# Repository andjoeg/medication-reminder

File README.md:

# medication-reminder
A device that reminds you to take medications based on a configurable daily schedule.

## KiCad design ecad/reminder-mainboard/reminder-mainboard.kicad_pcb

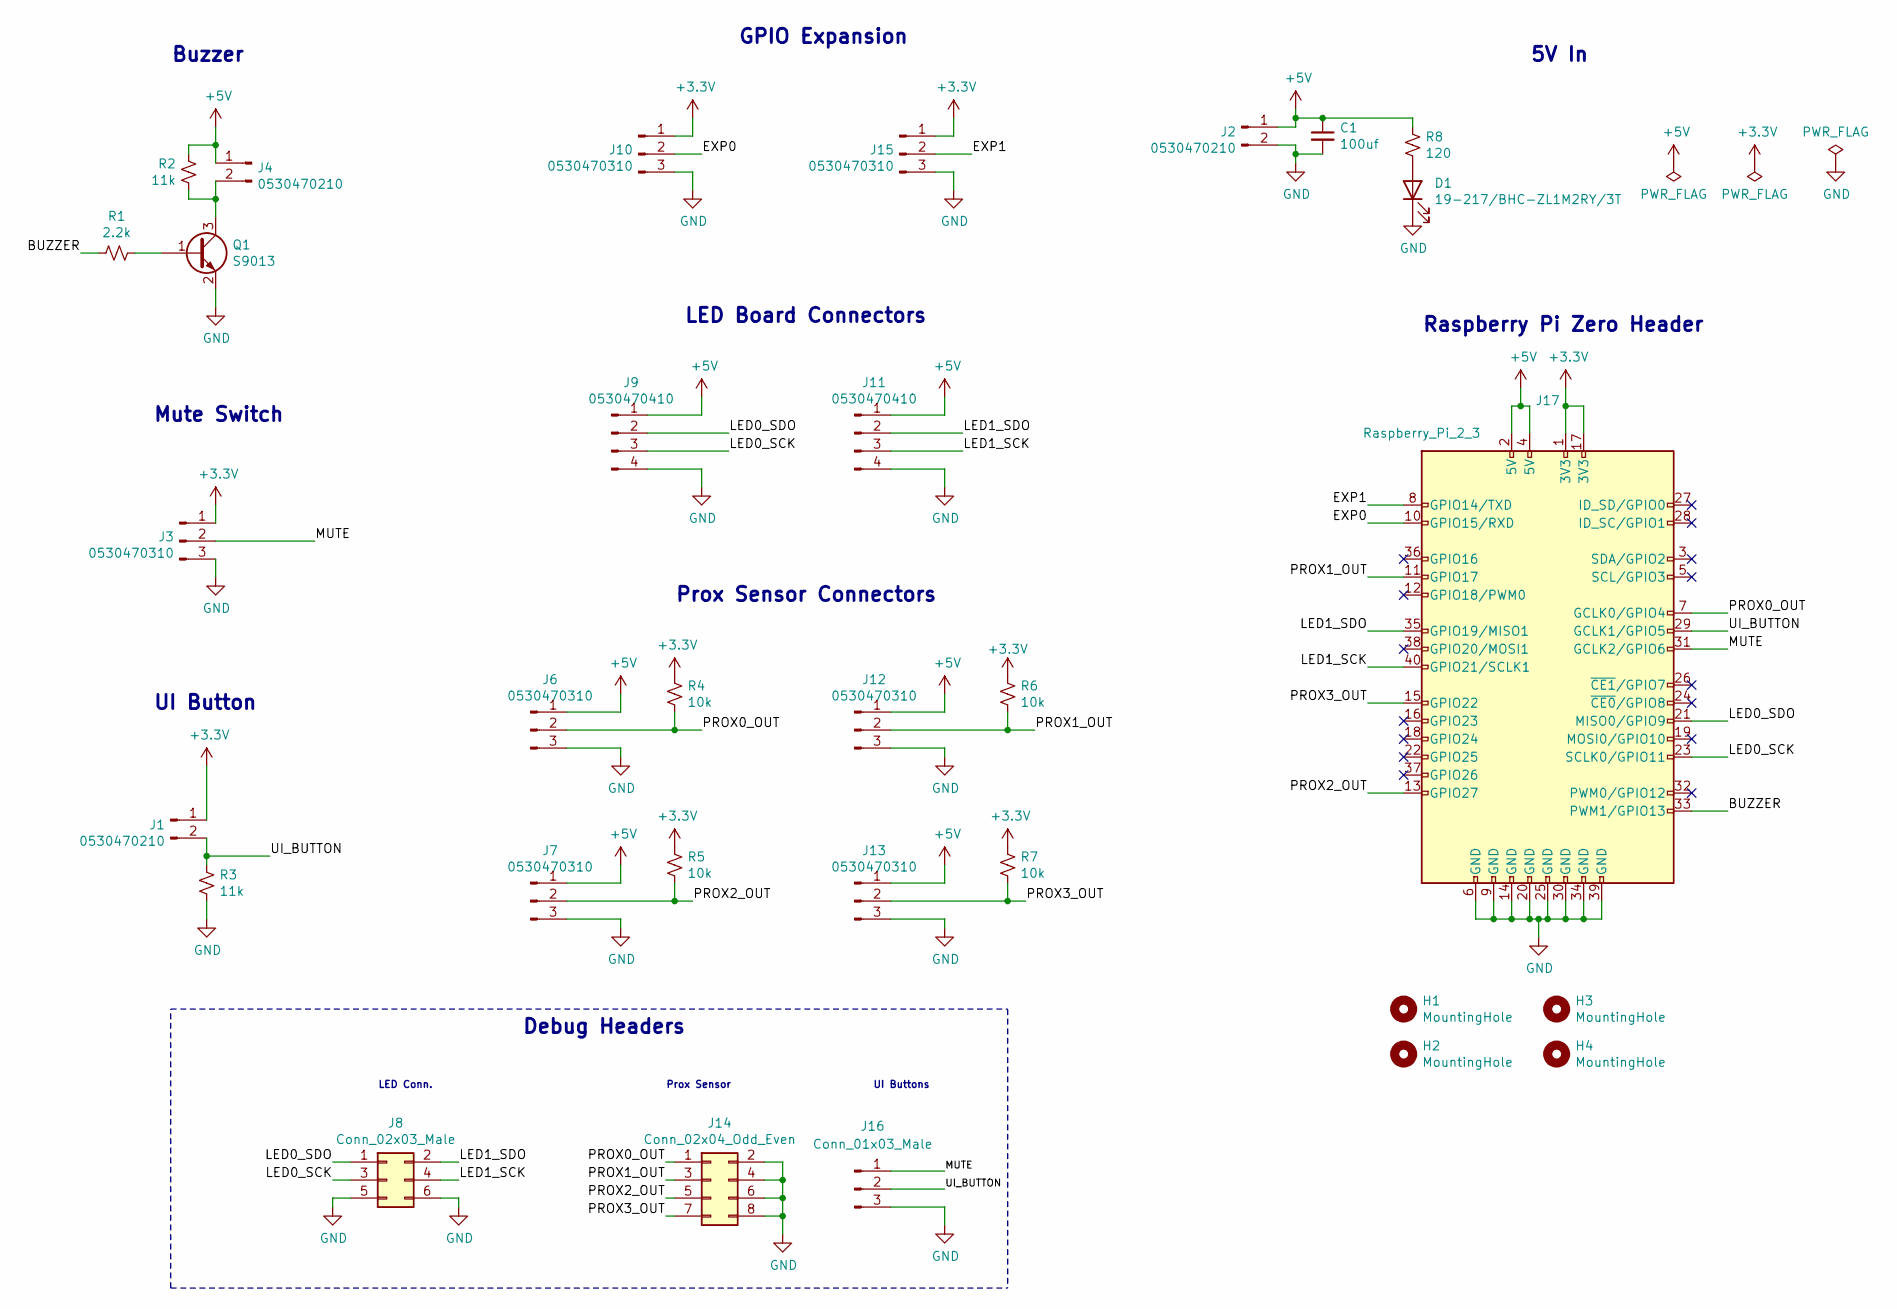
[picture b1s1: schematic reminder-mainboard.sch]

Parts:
C1: 100uf; CP_EIA-3528-21_Kemet-B; LCSC Part Number C16133
D1: 19-217/BHC-ZL1M2RY/3T; LED_0603_1608Metric; LCSC Part Number C72041
H1, H2, H3, H4: MountingHole; MountingHole_2.7mm_M2.5
J1, J2, J4: 0530470210; Molex_PicoBlade_53047-0210_1x02_P1.25mm_Vertical
J3, J6, J7, J10, J12, J13, J15: 0530470310; Molex_PicoBlade_53047-0310_1x03_P1.25mm_Vertical
J8: Conn_02x03_Male; PinHeader_2x03_P2.54mm_Vertical
J9, J11: 0530470410; Molex_PicoBlade_53047-0410_1x04_P1.25mm_Vertical
J14: Conn_02x04_Odd_Even; PinHeader_2x04_P2.54mm_Vertical
J16: Conn_01x03_Male; PinHeader_1x03_P2.54mm_Vertical
J17: Raspberry_Pi_2_3; PinSocket_2x20_P2.54mm_Vertical
Q1: S9013; SOT-23; LCSC Part Number C6749
R1: 2.2k; R_0603_1608Metric; LCSC Part Number C4190
R2, R3: 11k; R_0603_1608Metric; LCSC Part Number C25950
R4, R5, R6, R7: 10k; R_1206_3216Metric; LCSC Part Number C17902
R8: 120; R_0603_1608Metric; LCSC Part Number C22787

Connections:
+3V3: J1.1, J3.1, J10.1, J15.1, J17.1 (3V3), J17.17 (3V3), R4.1, R5.1, R6.1, R7.1
+5V: C1.1, J2.1, J4.1, J6.1, J7.1, J9.1, J11.1, J12.1, J13.1, J17.2 (5V), J17.4 (5V), R2.1, R8.1
/BUZZER: J17.33 (PWM1/GPIO13), R1.1
/EXP0: J10.2, J17.10 (GPIO15/RXD)
/EXP1: J15.2, J17.8 (GPIO14/TXD)
/LED0_SCK: J8.3, J9.3, J17.23 (SCLK0/GPIO11)
/LED0_SDO: J8.1, J9.2, J17.21 (MISO0/GPIO9)
/LED1_SCK: J8.4, J11.3, J17.40 (GPIO21/SCLK1)
/LED1_SDO: J8.2, J11.2, J17.35 (GPIO19/MISO1)
/MUTE: J3.2, J16.1, J17.31 (GCLK2/GPIO6)
/PROX0_OUT: J6.2, J14.1, J17.7 (GCLK0/GPIO4), R4.2
/PROX1_OUT: J12.2, J14.3, J17.11 (GPIO17), R6.2
/PROX2_OUT: J7.2, J14.5, J17.13 (GPIO27), R5.2
/PROX3_OUT: J13.2, J14.7, J17.15 (GPIO22), R7.2
/UI_BUTTON: J1.2, J16.2, J17.29 (GCLK1/GPIO5), R3.1
GND: C1.2, D1.1 (K), J2.2, J3.3, J6.3, J7.3, J8.5, J8.6, J9.4, J10.3, J11.4, J12.3, J13.3, J14.2, J14.4, J14.6, J14.8, J15.3, J16.3, J17.6 (GND), J17.9 (GND), J17.14 (GND), J17.20 (GND), J17.25 (GND), J17.30 (GND), J17.34 (GND), J17.39 (GND), Q1.2 (E), R3.2
unnamed: D1.2 (A), R8.2
unnamed: J4.2, Q1.3 (C), R2.2
unnamed: Q1.1 (B), R1.2

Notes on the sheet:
UI Button
Mute Switch
Buzzer
Prox Sensor Connectors
GPIO Expansion
LED Board Connectors
Debug Headers
LED Conn.
Prox Sensor
UI Buttons
5V In
Raspberry Pi Zero Header

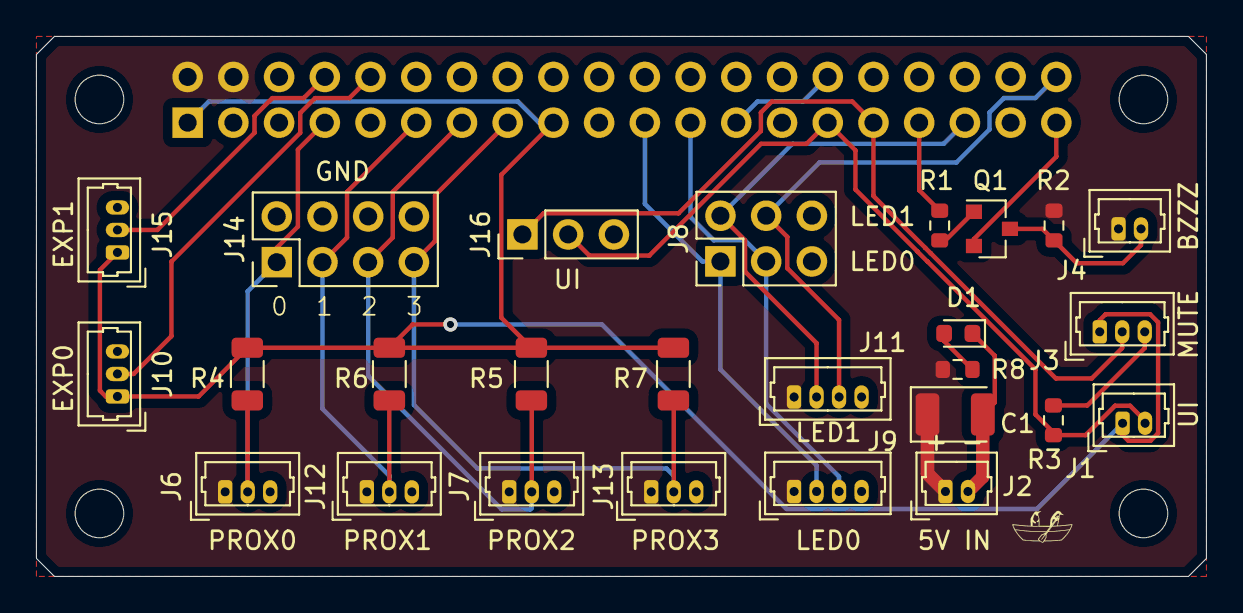
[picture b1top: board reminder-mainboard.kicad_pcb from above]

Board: 2 copper layers, 65.0 x 30.0 mm, 31 parts (1 on the bottom side), 19 nets.

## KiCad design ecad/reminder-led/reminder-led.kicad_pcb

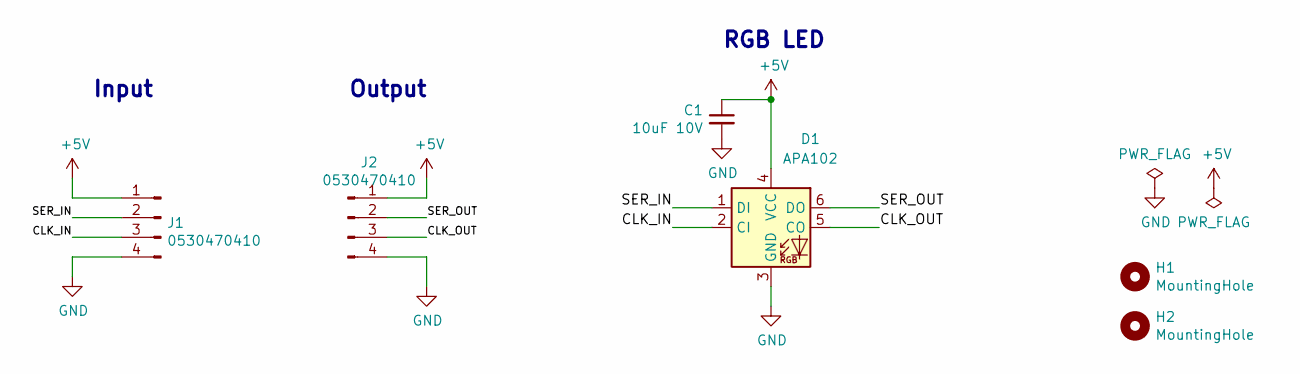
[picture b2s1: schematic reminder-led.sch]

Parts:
C1: 10uF 10V; C_Rect_L7.0mm_W2.0mm_P5.00mm
D1: APA102; LED_RGB_5050-6
H1, H2: MountingHole; MountingHole_2.7mm_M2.5_Pad
J1, J2: 0530470410; Molex_PicoBlade_53047-0410_1x04_P1.25mm_Vertical

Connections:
+5V: C1.1, D1.4 (VCC), J1.1, J2.1
/CLK_IN: D1.2 (CI), J1.3
/CLK_OUT: D1.5 (CO), J2.3
/SER_IN: D1.1 (DI), J1.2
/SER_OUT: D1.6 (DO), J2.2
GND: C1.2, D1.3 (GND), J1.4, J2.4

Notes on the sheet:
RGB LED
Input
Output

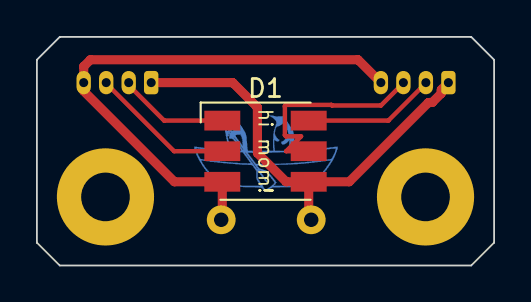
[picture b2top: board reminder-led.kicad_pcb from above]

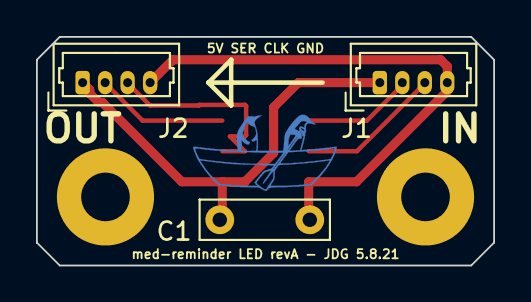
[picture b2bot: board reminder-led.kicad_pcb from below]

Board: 2 copper layers, 25.4 x 12.7 mm, 6 parts (3 on the bottom side), 6 nets.

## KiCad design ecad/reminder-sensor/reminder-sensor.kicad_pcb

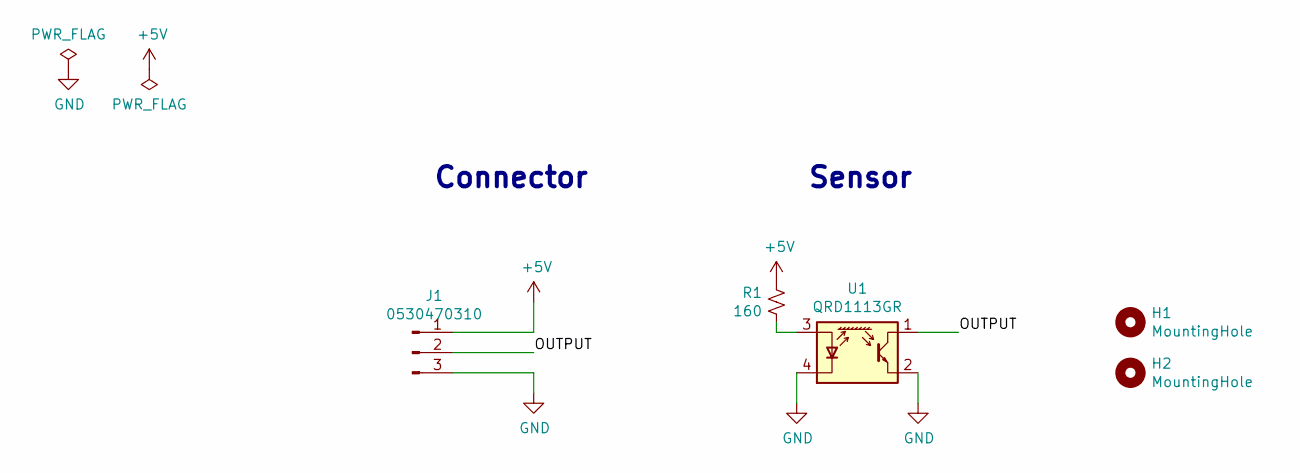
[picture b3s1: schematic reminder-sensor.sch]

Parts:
H1, H2: MountingHole; MountingHole_2.2mm_M2
J1: 0530470310; Molex_PicoBlade_53047-0310_1x03_P1.25mm_Vertical
R1: 160; R_1206_3216Metric
U1: QRD1113GR; Everlight_ITR8307F43

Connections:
+5V: J1.1, R1.1
/OUTPUT: J1.2, U1.1 (C)
GND: J1.3, U1.2 (E), U1.4 (K)
unnamed: R1.2, U1.3 (A)

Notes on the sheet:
Sensor
Connector

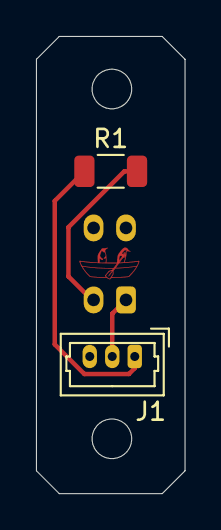
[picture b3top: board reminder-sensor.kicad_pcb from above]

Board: 2 copper layers, 8.3 x 25.4 mm, 5 parts (1 on the bottom side), 4 nets.

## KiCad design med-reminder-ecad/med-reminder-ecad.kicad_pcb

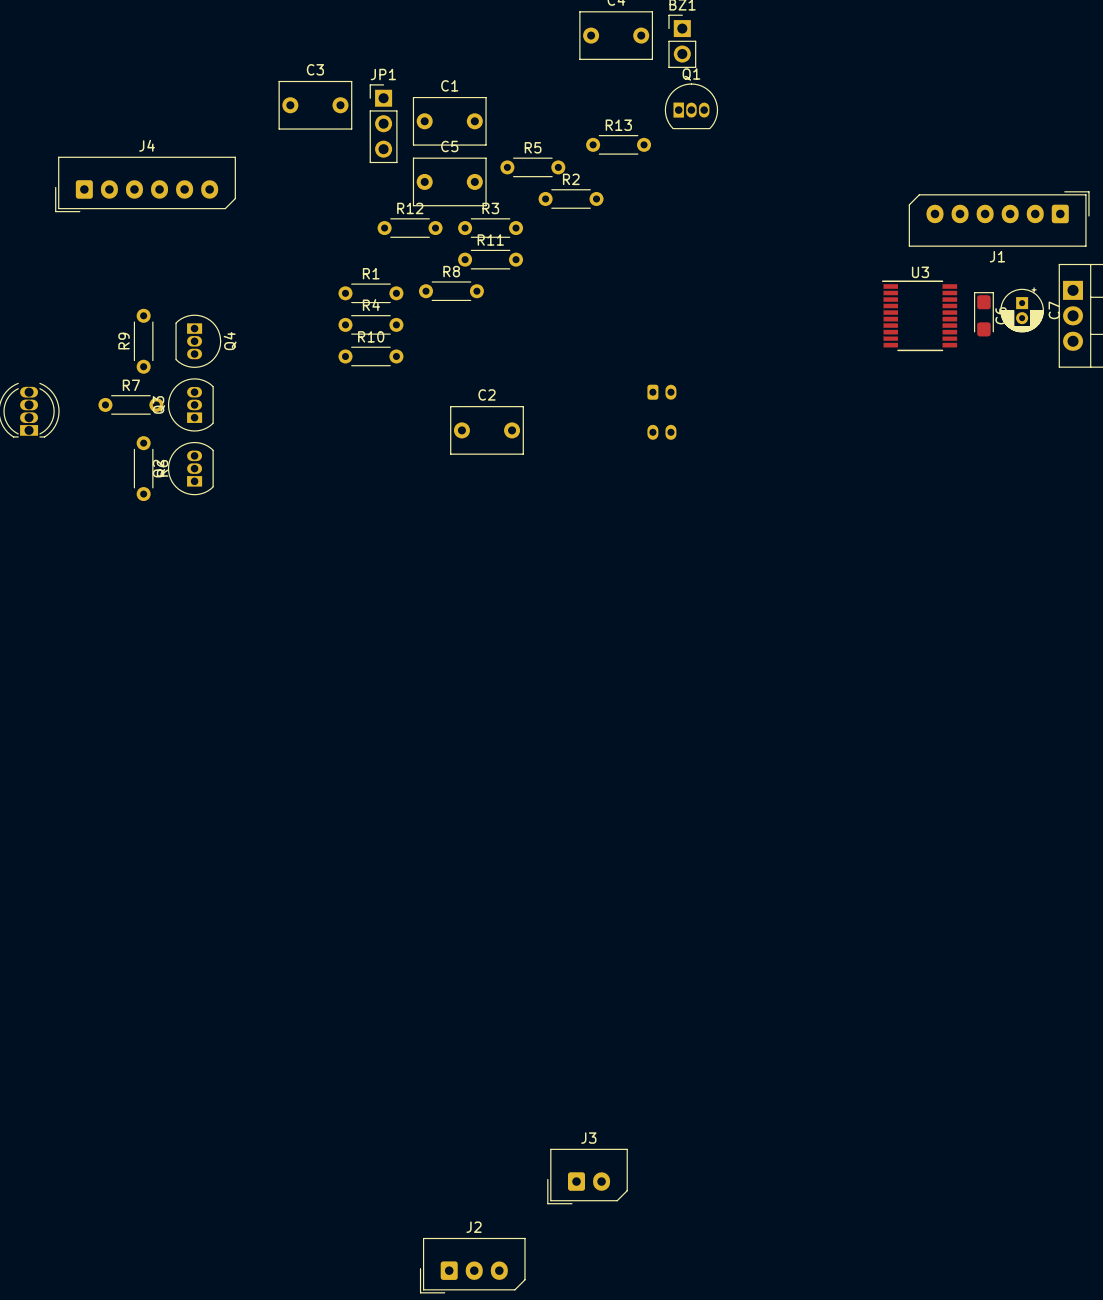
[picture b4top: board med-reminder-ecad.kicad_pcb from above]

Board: 2 copper layers, 34 parts (1 on the bottom side), 32 nets, no tracks yet.

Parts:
BZ1: PinHeader_1x02_P2.54mm_Vertical
C1, C2: 10uF; C_Rect_L7.0mm_W4.5mm_P5.00mm
C3, C4: 20pF; C_Rect_L7.0mm_W4.5mm_P5.00mm
C5: 100nF; C_Rect_L7.0mm_W4.5mm_P5.00mm
C6: 100nF; CP_EIA-3216-10_Kemet-I
C7: 4.7uF; CP_Radial_D4.0mm_P1.50mm
D1: LED_RGBA; LED_D5.0mm-4_RGB
J1: USB_B_Micro; Molex_SPOX_5267-06A_1x06_P2.50mm_Vertical
J2: 22-03-5035; Molex_SPOX_5267-03A_1x03_P2.50mm_Vertical
J3: 22-03-5025; Molex_SPOX_5267-02A_1x02_P2.50mm_Vertical
J4: 22-03-5065; Molex_SPOX_5267-06A_1x06_P2.50mm_Vertical
JP1: Jumper_3_Bridged12; PinHeader_1x03_P2.54mm_Vertical
Q1, Q2, Q3, Q4: 2N3904; TO-92_Inline
R1, R3, R4, R5: 620; R_Axial_DIN0204_L3.6mm_D1.6mm_P5.08mm_Horizontal
R2, R8, R12, R13: 10k; R_Axial_DIN0204_L3.6mm_D1.6mm_P5.08mm_Horizontal
R6: 130; R_Axial_DIN0204_L3.6mm_D1.6mm_P5.08mm_Horizontal
R7, R9: 91; R_Axial_DIN0204_L3.6mm_D1.6mm_P5.08mm_Horizontal
R10: 180; R_Axial_DIN0204_L3.6mm_D1.6mm_P5.08mm_Horizontal
R11: 390; R_Axial_DIN0204_L3.6mm_D1.6mm_P5.08mm_Horizontal
U1: LM1117-3.3; TO-220-3_Vertical
U2: QRD1113GR; Everlight_ITR8307F43
U3: STM32F042F4Px; TSSOP-20_4.4x6.5mm_P0.65mm

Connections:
+3V3: C2.1, C6.1, C7.1, J2.1, J3.1, J4.1, JP1.3, R12.1, U1.2, U3.5, U3.16
+5V: BZ1.1, C1.1, D1.4, J1.1, R2.1, R10.1, U1.3
/BUZZER: R1.1, U3.12
/LED_B: R5.1, U3.9
/LED_G: R4.1, U3.8
/LED_R: R3.1, U3.7
/MUTE: J2.2, U3.11
/NRST: C5.1, J4.5, U3.4
/SENSOR: R12.2, U2.1, U3.13
/SWCLK: J4.2, U3.20
/SWDIO: J4.4, U3.19
/UI_BUTTON: J3.2, R8.1, U3.10
/USB_M: J1.2, U3.17
/USB_P: J1.3, U3.18
GND: C1.2, C2.2, C3.2, C4.2, C5.2, C6.2, C7.2, J1.5, J2.3, J4.3, JP1.1, Q1.1, Q2.1, Q3.1, Q4.1, R8.2, U1.1, U2.2, U2.4, U3.15
unnamed: BZ1.2, Q1.3, R2.2
unnamed: C3.1, U3.2
unnamed: C4.1, R11.2
unnamed: D1.1, R6.1
unnamed: D1.2, R7.1
unnamed: D1.3, R9.1
unnamed: JP1.2, R13.2
unnamed: Q1.2, R1.2
unnamed: Q2.2, R3.2
unnamed: Q2.3, R6.2
unnamed: Q3.2, R4.2
unnamed: Q3.3, R7.2
unnamed: Q4.2, R5.2
unnamed: Q4.3, R9.2
unnamed: R10.2, U2.3
unnamed: R11.1, U3.3
unnamed: R13.1, U3.1

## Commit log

2021-03-02 Initial schematic capture.
2021-03-02 Changed OSC footprint size, changed switch footprint.
2021-03-10 WIP update for PCB layout
2021-03-13 Removed oscillator circuit
2021-03-14 Changed footprint of UI elements to be MOLEX SL connectors
2021-03-14 Broke out LED board to heirarchal sheet to become a separate board, replaced some components with SMD
2021-03-14 Added gitignore
2021-03-14 Added sheet for LED daughterboard
2021-03-14 Broke out file structure for separate boards
2021-03-14 Broke out separate board for LED
2021-03-15 Began SMD layout
2021-03-17 Finished routing
2021-04-22 Readied for adding separate usb chip
2021-04-26 Started work on RPI-hat version
2021-04-26 Started sensor board design
2021-04-28 Changed sensor pinout to 3 pin connector
2021-05-04 Finished sensor board schematic
2021-05-04 Added penguin
2021-05-04 Finished routing, silkscreen details.
2021-05-04 Changed LED board type to 5050 LED
2021-05-08 Finished LED board routing and detailing
2021-05-08 Added rev text and chamfered corners of PCB
2021-05-08 Finished mainboard schematic layout
2021-05-09 Finished mainboard pcb routing
2021-05-09 Changed pin assignments for cleaner PCB routing
2021-05-09 PCB routing changes
2021-05-09 Added LCSC part numbers, minor tweaks based on part availablity.
2021-05-11 Created production files and gerbers
2021-05-11 Added gerber zip
